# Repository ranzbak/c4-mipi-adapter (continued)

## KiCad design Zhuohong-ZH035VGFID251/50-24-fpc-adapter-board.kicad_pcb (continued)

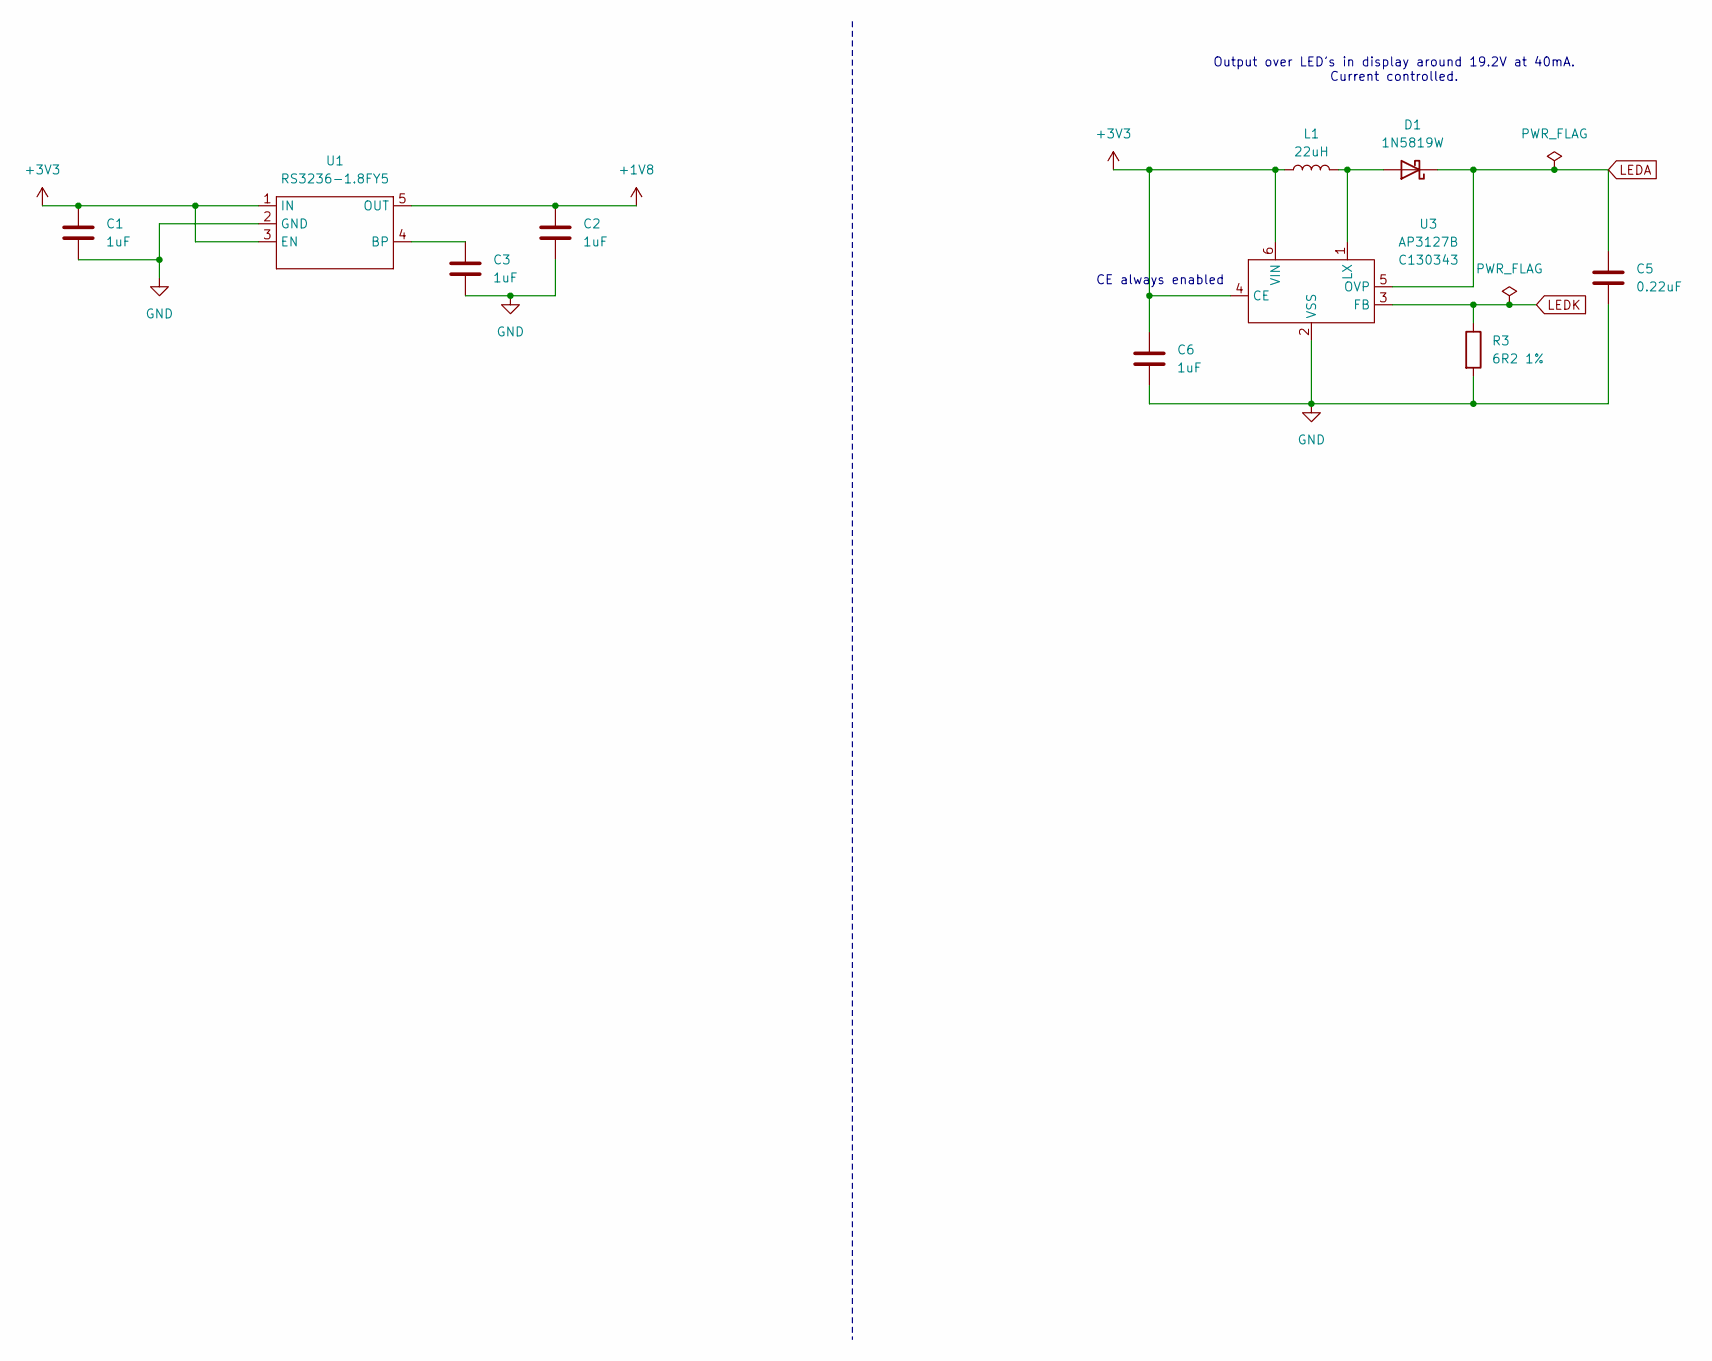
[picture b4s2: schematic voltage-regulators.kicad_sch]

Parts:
C1, C2, C3, C6: 1uF; C_0603_1608Metric; LCSC C5189821
C5: 0.22uF; C_0603_1608Metric
D1: 1N5819W; D_SOD-123; LCSC C402219
L1: 22uH; L_Changjiang_FNR252010S; LCSC C486445
R3: 6R2 1%; R_0603_1608Metric; lcsc C3013206
U1: RS3236-1.8FY5; SOT-23-5; Lcsc C379343
U3: AP3127B; SOT-23-6; LCSC C130343

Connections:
+1V8: C2.1, U1.5 (OUT); also elsewhere on the board
+3V3: C1.1, C6.1, L1.1, U1.1 (IN), U1.3 (EN), U3.4 (CE), U3.6 (VIN); also elsewhere on the board
GND: C1.2, C2.2, C3.2, C5.2, C6.2, R3.2, U1.2 (GND), U3.2 (VSS); also elsewhere on the board
LEDA: C5.1, D1.1 (K), U3.5 (OVP); also elsewhere on the board
LEDK: R3.1, U3.3 (FB); also elsewhere on the board
unnamed: D1.2 (A), L1.2, U3.1 (LX)
unnamed: C3.1, U1.4 (BP)

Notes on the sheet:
CE always enabled
Output over LED's in display around 19.2V at 40mA. Current controlled.

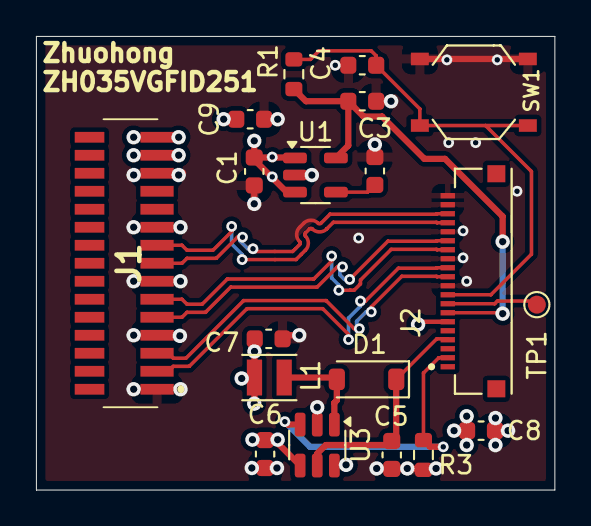
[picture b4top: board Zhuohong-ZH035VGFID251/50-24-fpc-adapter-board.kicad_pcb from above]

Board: 4 copper layers, 28.8 x 25.2 mm, 19 parts (0 on the bottom side), 15 nets.

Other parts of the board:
J1: 1-1734248-5; 117342485

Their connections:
+3V3: J1.14, J1.15; also elsewhere on the board
CLK_C_N: J1.5; also elsewhere on the board
CLK_C_P: J1.6; also elsewhere on the board
D0_N: J1.8; also elsewhere on the board
D0_P: J1.9; also elsewhere on the board
D1_N: J1.2; also elsewhere on the board
D1_P: J1.3; also elsewhere on the board
GND: J1.1, J1.4, J1.7, J1.10, J1.13; also elsewhere on the board

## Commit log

2024-04-16 Add swd-lh397kic01 board.
2024-04-17 Add LCSC numbers to C's and R's
2024-04-17 Add lcd-mall-LMT040WV004C board as well.
2024-04-18 Fix names, footprints, and silkscreen of the pcb's
2024-05-08 Add LCSC labels that were missing for swd lh397kic01
2024-05-08 Fix parts for board LMT040WM004C
2024-05-08 Fixed lmt040wv004c board for production @ JLCPCB
